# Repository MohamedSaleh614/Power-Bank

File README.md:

# 🔋 DIY Li-Ion Power Bank

A compact power bank project combining battery charging, protection, and voltage conversion.

### ⚙️ Main Components
- **LTC4054:** Li-ion battery charger
- **BMS:** Battery protection
- **MC34063A:** Boost converter

### 🔌 Working Principle
1. Charge the Li-ion battery through the LTC4054.
2. Use the BMS for battery protection.
3. Boost the battery voltage to 5V using the MC34063A.

### 🎯 Goal
Build a practical power bank using individual electronic circuit stages.

### 🛠️ Project Status
DIY electronics project. Test the output voltage, current capability, and protection functions before connecting devices.

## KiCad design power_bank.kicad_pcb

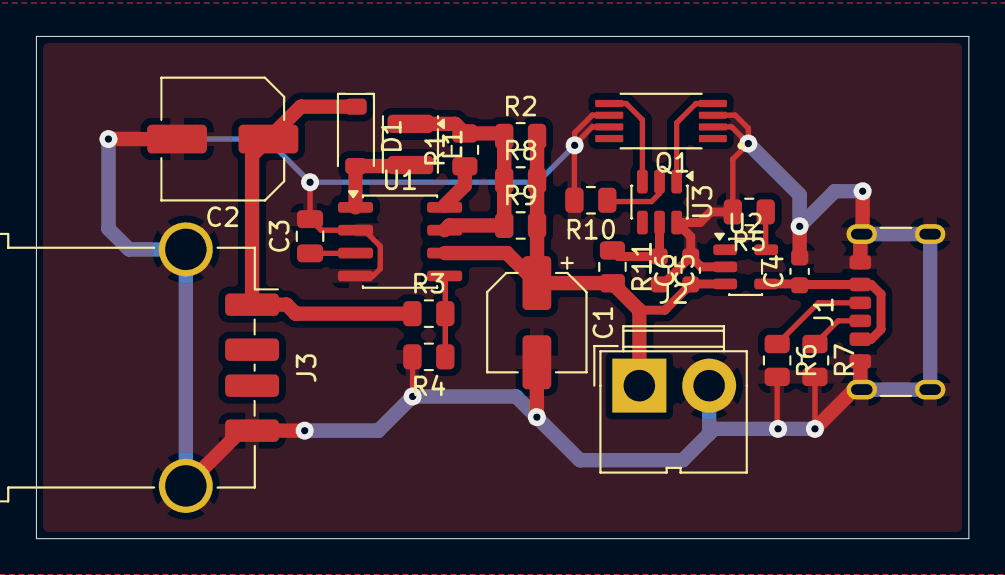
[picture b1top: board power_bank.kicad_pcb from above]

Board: 2 copper layers, 51.8 x 27.9 mm, 26 parts (0 on the bottom side), 16 nets.

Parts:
C1: 100u; CP_Elec_5x5.4
C2: 220u; C_Elec_6.3x7.7
C3: 470p; C_0805_2012Metric
C4: 1u; C_0603_1608Metric
C5: 0.1u; C_0603_1608Metric
C6: 10u; C_0603_1608Metric
D1: D; D_SOD-123
J1: USB_C_Receptacle_PowerOnly_6P; USB_C_Receptacle_GCT_USB4125-xx-x-0190_6P_TopMnt_Horizontal
J2: Conn_01x02_Pin; JWT_A3963_1x02_P3.96mm_Vertical
J3: USB_A; USB_A_TE_292303-7_Horizontal
L1: 100u; L_Coilcraft_1008HQ_2520Metric
Q1: FS8205A; SOP65P640X120-8N
R1: 180; R_0805_2012Metric
R2, R8, R9: 0.47; R_0805_2012Metric
R3: 6k; R_0805_2012Metric
R4: 2k; R_0805_2012Metric
R5: 1.5k; R_0805_2012Metric
R6, R7: 5k; R_0805_2012Metric
R10: 1k; R_0805_2012Metric
R11: 100; R_0805_2012Metric
U1: MC34063AD; SOIC-8_3.9x4.9mm_P1.27mm
U2: LTC4054ES5-4.2; TSOT-23-5
U3: DW01A; SOT-23-6

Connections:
/<NO NET>: C4.1, J1.A9 (VBUS), J1.B9 (VBUS), U2.4 (V_{CC})
/BAT: C1.1, C6.1, J2.1, R2.2, R8.2, R9.2, R11.2, U1.6 (Vin), U2.3 (BAT)
/CC1: J1.A5 (CC1), R7.1
/CC2: J1.B5 (CC2), R6.1
/CS: R10.1, U3.2 (CS)
/DRC: R1.1, U1.8 (DC)
/IPK: L1.1, R1.2, R2.1, R8.1, R9.1, U1.7 (Ipk)
/OC: Q1.5, U3.3 (OC)
/OD: Q1.4, U3.1 (OD)
/PROG: R5.1, U2.5 (PROG)
/SWC: D1.2 (A), L1.2, U1.1 (SwC)
/TC: C3.1, U1.3 (TC)
/VCC2: C5.1, R11.1, U3.5 (VCC)
/VFB: R3.2, R4.1, U1.5 (Vfb)
/VOUT: C2.1, D1.1 (K), J3.1 (VBUS), R3.1
GND: C1.2, C2.2, C3.2, C4.2, C5.2, C6.2, J1.A12 (GND), J1.B12 (GND), J1.SH (SHIELD), J2.2, J3.4 (GND), J3.SH (Shield), Q1.2, Q1.3, Q1.6, Q1.7, R4.2, R5.2, R6.2, R7.2, R10.2, U1.2 (SwE), U1.4 (GND), U2.2 (GND), U3.6 (GND)
